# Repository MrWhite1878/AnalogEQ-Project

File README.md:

# AnalogEQ-Project
This repo serves to document relevant information on the design of an analog audio equalizer, whose goal is to serve as a learning tool and correctional component for my desktop speakers.
<!-- Photo -->
> WARNING: This project is a work in progress.
> Nothing is finalized, and this repo mainly serves to document and catalog my journey.

### Target Specifications
*	RCA audio input/output (adapters included)
*	9VAC Wall Wart power input
* ±18VDC rails powering NE5532 and TL072 op amps
* Smooth knobs for all controls
* High input impedance and low output impedance
* Audio bypass switch
* Input and Output Amplification
* 3rd order butterworth BPF for frequencies outside 20Hz-20kHz
* Sharp (Q = 10) -15dB Notch filter with adjustable target frequency (35-85Hz)
* LF and HF shelving with adjustable gain (±16dB) and proportional break/corner frequency
* 2 fully parametric middle controls: ±15dB gain, 70Hz-1.5kHz range 1 and 700-15kHz range 2, 0.5 < Q < 5
* Diagnostic board LEDs and testing pads

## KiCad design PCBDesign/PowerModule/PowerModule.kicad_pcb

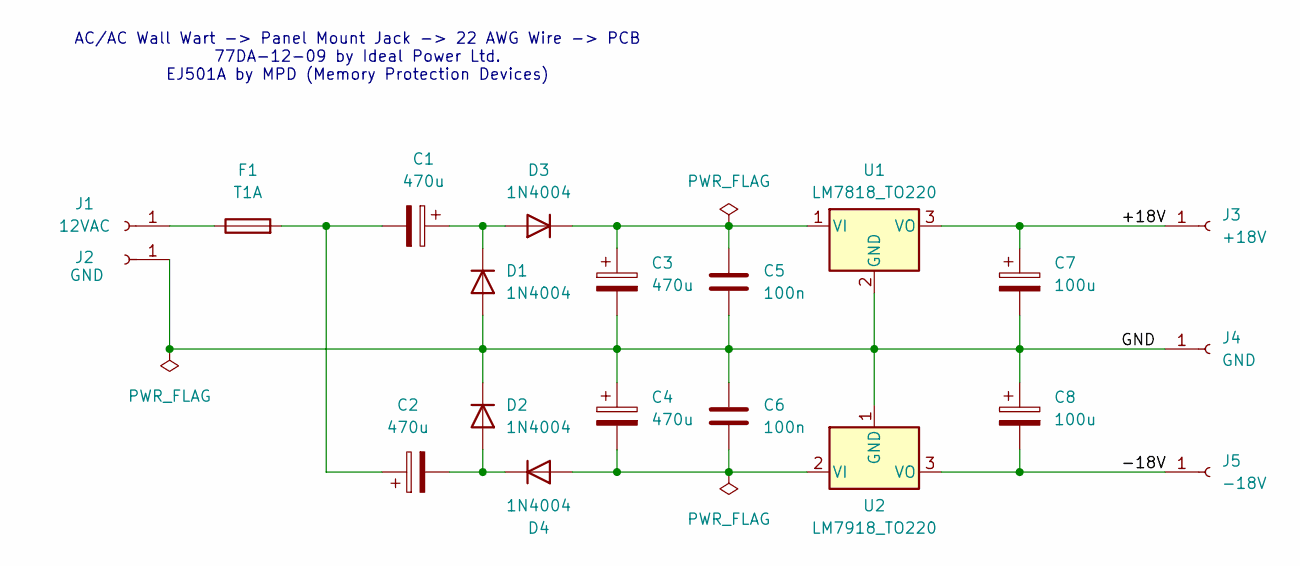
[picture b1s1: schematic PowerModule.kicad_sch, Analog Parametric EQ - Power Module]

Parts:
C1, C2, C3, C4: 470u; CP_Radial_D10.0mm_P5.00mm; MPN 50ZLJ470M10X20
C5, C6: 100n; C_Disc_D3.8mm_W2.6mm_P2.50mm; MPN K104K10X7RF53L2
C7, C8: 100u; CP_Radial_D8.0mm_P3.50mm; MPN 50ZLJ100M8X11.5
D1, D2, D3, D4: 1N4004; D_DO-41_SOD81_P10.16mm_Horizontal; MPN 1N4004G
F1: T1A; Fuse_BelFuse_0697H; MPN 0697H1000-02
J1: 12VAC; SolderWire-0.5sqmm_1x01_D0.9mm_OD2.1mm_Relief
J2, J4: GND; SolderWire-0.5sqmm_1x01_D0.9mm_OD2.1mm_Relief
J3: +18V; SolderWire-0.5sqmm_1x01_D0.9mm_OD2.1mm_Relief
J5: -18V; SolderWire-0.5sqmm_1x01_D0.9mm_OD2.1mm_Relief
U1: LM7818_TO220; TO-220-3_Vertical; MPN MC7818CTG
U2: LM7918_TO220; TO-220-3_Vertical; MPN MC7918CTG

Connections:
/+18V: C7.1, J3.1 (Pin_1_1), U1.3 (VO)
/-18V: C8.2, J5.1 (Pin_1_1), U2.3 (VO)
/GND: C3.2, C4.1, C5.2, C6.1, C7.2, C8.1, D1.2 (A), D2.1 (K), J2.1 (Pin_1_1), J4.1 (Pin_1_1), U1.2 (GND), U2.1 (GND)
unnamed: C1.2, C2.1, F1.2
unnamed: C1.1, D1.1 (K), D3.2 (A)
unnamed: C2.2, D2.2 (A), D4.1 (K)
unnamed: C3.1, C5.1, D3.1 (K), U1.1 (VI)
unnamed: C4.2, C6.2, D4.2 (A), U2.2 (VI)
unnamed: F1.1, J1.1 (Pin_1_1)

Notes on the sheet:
AC/AC Wall Wart -> Panel Mount Jack -> 22 AWG Wire -> PCB 77DA-12-09 by Ideal Power Ltd. EJ501A by MPD (Memory Protection Devices)

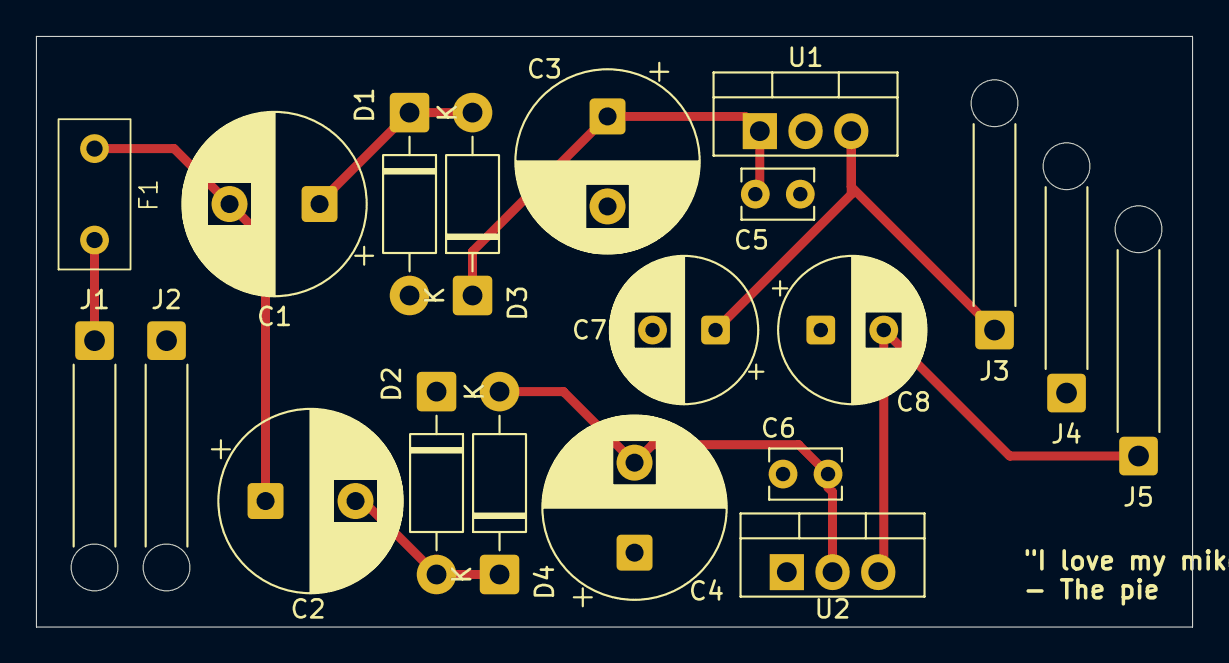
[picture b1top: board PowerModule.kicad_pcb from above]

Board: 2 copper layers, 64.2 x 32.8 mm, 20 parts (0 on the bottom side), 9 nets.

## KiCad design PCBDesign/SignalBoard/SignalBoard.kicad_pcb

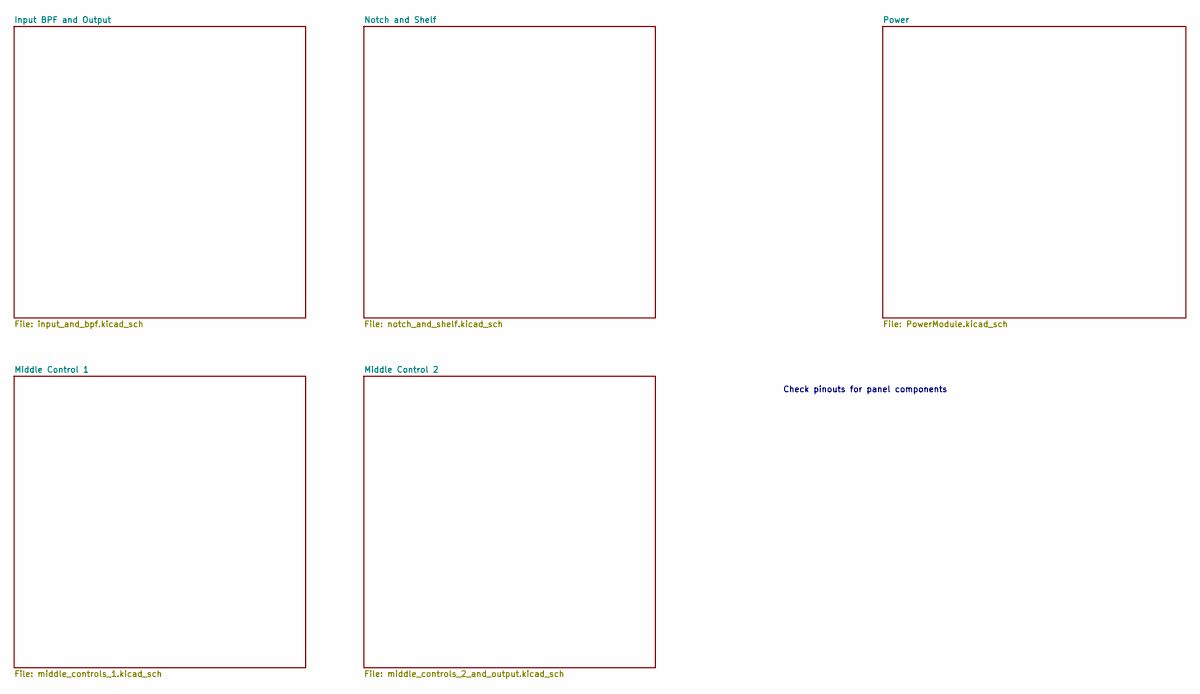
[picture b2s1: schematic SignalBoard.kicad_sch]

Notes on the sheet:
Check pinouts for panel components

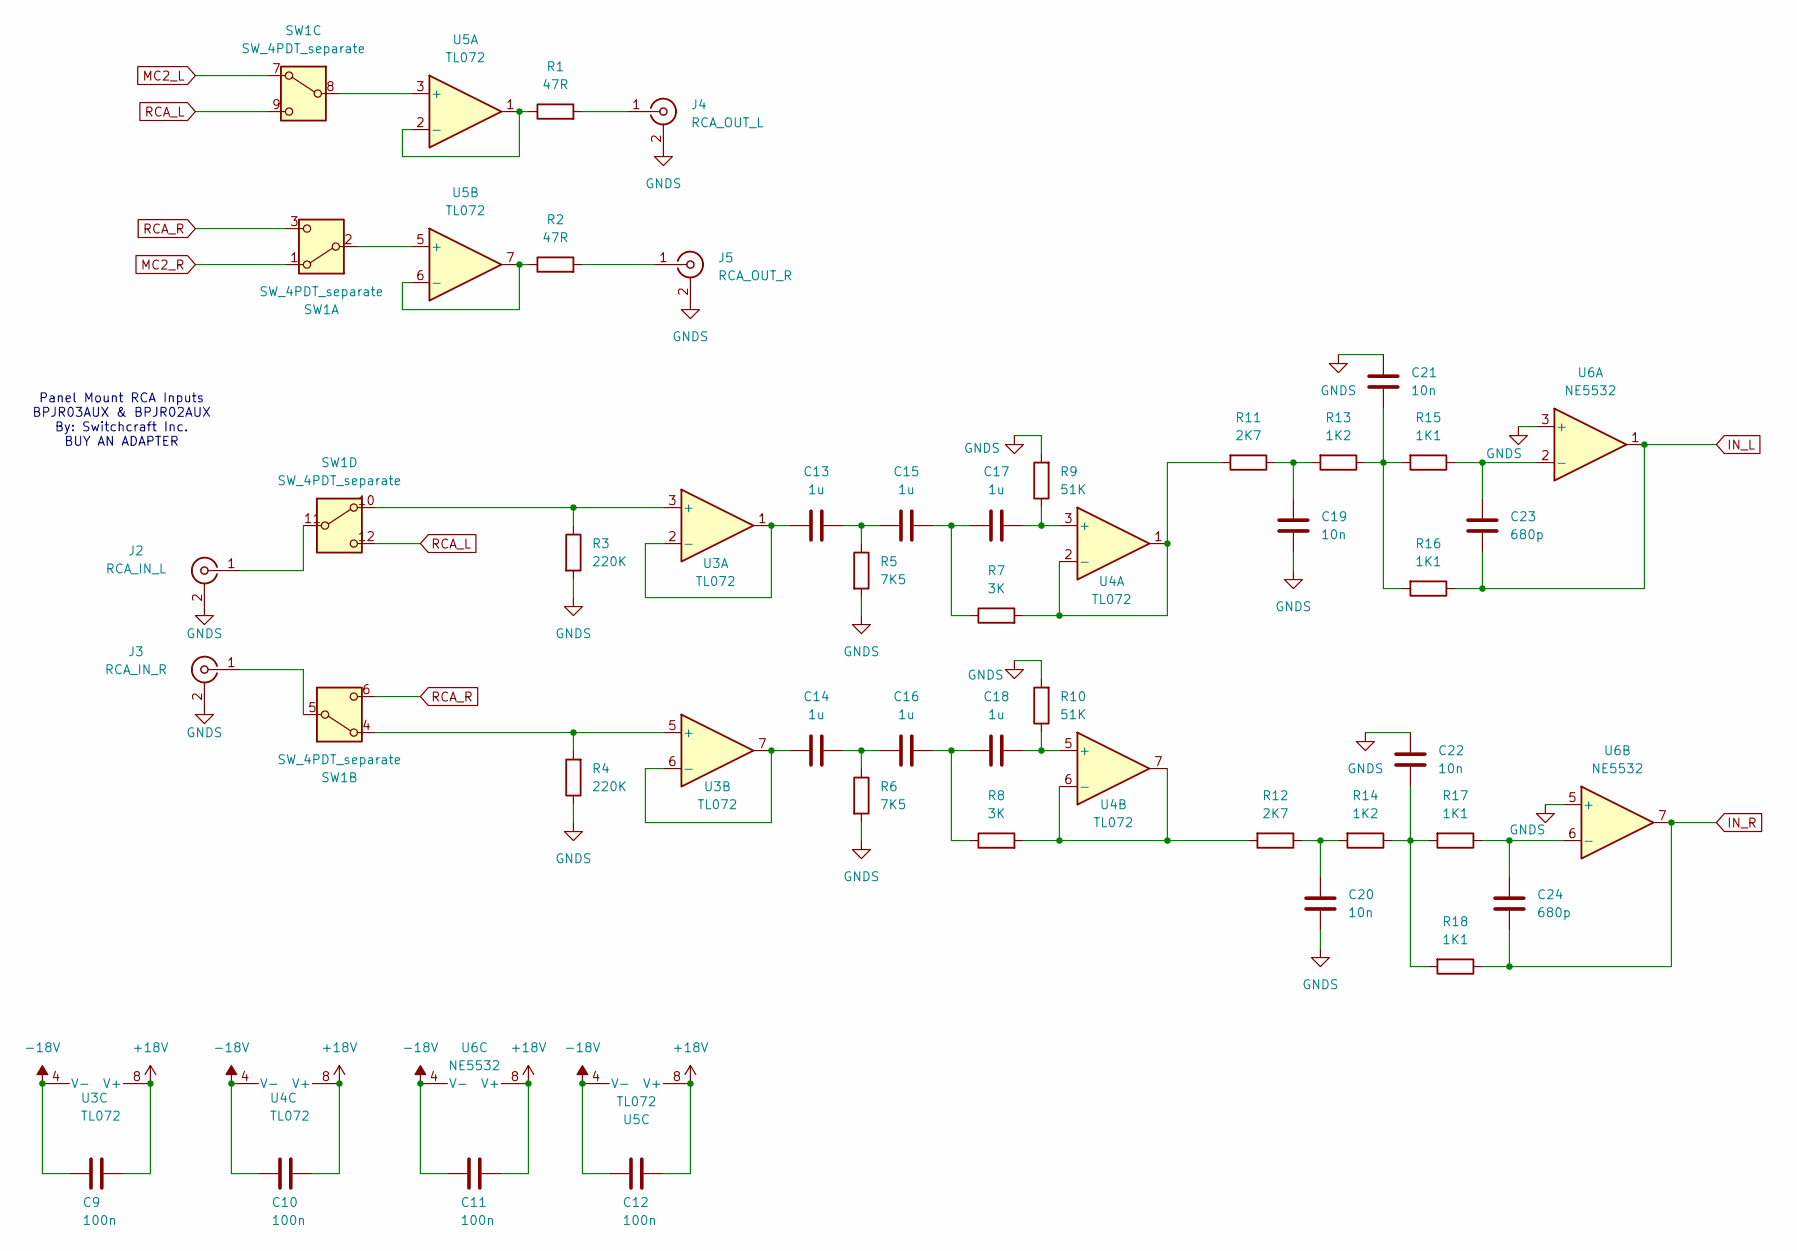
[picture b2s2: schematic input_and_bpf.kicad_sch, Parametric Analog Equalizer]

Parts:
C9, C10, C11, C12: 100n; C_0805_2012Metric_Pad1.18x1.45mm_HandSolder; MPN CL21B104KCFNNNE; Digikey PN 1276-6840-1-ND
C13, C14, C15, C16, C17, C18: 1u; C_Rect_L18.0mm_W7.0mm_P15.00mm_FKS3_FKP3; MPN ECW-FE2W105JA
C19, C20, C21, C22: 10n; C_1206_3216Metric_Pad1.33x1.80mm_HandSolder; MPN CC1206JKNPO0BN103; Digikey PN 311-4374-1-ND
C23, C24: 680p; C_1206_3216Metric_Pad1.33x1.80mm_HandSolder; MPN CC1206JRNPOYBN681; Digikey PN 13-CC1206JRNPOYBN681CT-ND
J2: RCA_IN_L; KLPX-0848A-2-; MPN KLPX-0848A-2-W
J3: RCA_IN_R; KLPX-0848A-2-; MPN KLPX-0848A-2-R
J4: RCA_OUT_L; KLPX-0848A-2-; MPN KLPX-0848A-2-W
J5: RCA_OUT_R; KLPX-0848A-2-; MPN KLPX-0848A-2-R
R1, R2: 47R; R_1206_3216Metric_Pad1.30x1.75mm_HandSolder; MPN RT1206FRE0747RL; Digikey PN 13-RT1206FRE0747RLCT-ND
R3, R4: 220K; R_1206_3216Metric_Pad1.30x1.75mm_HandSolder; MPN RT1206FRE07220KL; Digikey PN 13-RT1206FRE07220KLCT-ND
R5, R6: 7K5; R_1206_3216Metric_Pad1.30x1.75mm_HandSolder; MPN RT1206FRE077K5L; Digikey PN 13-RT1206FRE077K5LCT-ND
R7, R8: 3K; R_1206_3216Metric_Pad1.30x1.75mm_HandSolder; MPN RT1206DRD073KL; Digikey PN 13-RT1206DRD073KLCT-ND
R9, R10: 51K; R_1206_3216Metric_Pad1.30x1.75mm_HandSolder; MPN RT1206DRD0751KL; Digikey PN 13-RT1206DRD0751KLCT-ND
R11, R12: 2K7; R_1206_3216Metric_Pad1.30x1.75mm_HandSolder; MPN RT1206DRE072K7L; Digikey PN 311-2985-1-ND
R13, R14: 1K2; R_1206_3216Metric_Pad1.30x1.75mm_HandSolder; MPN RT1206FRE071K2L; Digikey PN 13-RT1206FRE071K2LCT-ND
R15, R16, R17, R18: 1K1; R_1206_3216Metric_Pad1.30x1.75mm_HandSolder; MPN RT1206FRE071K1L; Digikey PN 13-RT1206FRE071K1LCT-ND
SW1: SW_4PDT_separate; 1004P1T1B9M7QEH; MPN 1004P1T1B9M7QEH
U3, U4, U5: TL072; DIP-8_W7.62mm_LongPads; MPN TL072BCP
U6: NE5532; DIP-8_W7.62mm_LongPads; MPN NE5532P

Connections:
+18V: C9.1, C10.1, C11.1, C12.1, U3.8 (V+), U4.8 (V+), U5.8 (V+), U6.8 (V+); also elsewhere on the board
-18V: C9.2, C10.2, C11.2, C12.2, U3.4 (V-), U4.4 (V-), U5.4 (V-), U6.4 (V-); also elsewhere on the board
GNDS: C19.2, C20.2, C21.1, C22.1, J2.2 (Ext), J3.2 (Ext), J4.2 (Ext), J5.2 (Ext), R3.2, R4.1, R5.2, R6.2, R9.2, R10.2, U6.3 (+), U6.5 (+); also elsewhere on the board
IN_L: C23.2, R16.1, U6.1; also elsewhere on the board
IN_R: C24.2, R18.1, U6.7; also elsewhere on the board
MC2_L: SW1.7 (A); also elsewhere on the board
MC2_R: SW1.1 (A); also elsewhere on the board
unnamed: C13.2, C15.1, R5.1
unnamed: C14.2, C16.1, R6.1
unnamed: C15.2, C17.1, R7.1
unnamed: C16.2, C18.1, R8.1
unnamed: C19.1, R11.1, R13.2
unnamed: C20.1, R12.1, R14.2
unnamed: C21.2, R13.1, R15.2, R16.2
unnamed: C22.2, R14.1, R17.2, R18.2
unnamed: J2.1 (In), SW1.11 (B)
unnamed: J3.1 (In), SW1.5 (B)
unnamed: J4.1 (In), R1.2
unnamed: J5.1 (In), R2.2
unnamed: SW1.2 (B), U5.5 (+)
unnamed: R4.2, SW1.4 (A), U3.5 (+)
unnamed: SW1.8 (B), U5.3 (+)
unnamed: R3.1, SW1.10 (A), U3.3 (+)
unnamed: C13.1, U3.1, U3.2 (-)
unnamed: C14.1, U3.6 (-), U3.7
unnamed: C17.2, R9.1, U4.3 (+)
unnamed: R7.2, R11.2, U4.1, U4.2 (-)
unnamed: C18.2, R10.1, U4.5 (+)
unnamed: R8.2, R12.2, U4.6 (-), U4.7
unnamed: R1.1, U5.1, U5.2 (-)
unnamed: R2.1, U5.6 (-), U5.7
unnamed: C23.1, R15.1, U6.2 (-)
unnamed: C24.1, R17.1, U6.6 (-)
RCA_L: SW1.9 (C), SW1.12 (C)
RCA_R: SW1.3 (C), SW1.6 (C)

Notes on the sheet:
Panel Mount RCA Inputs BPJR03AUX & BPJR02AUX By: Switchcraft Inc. BUY AN ADAPTER

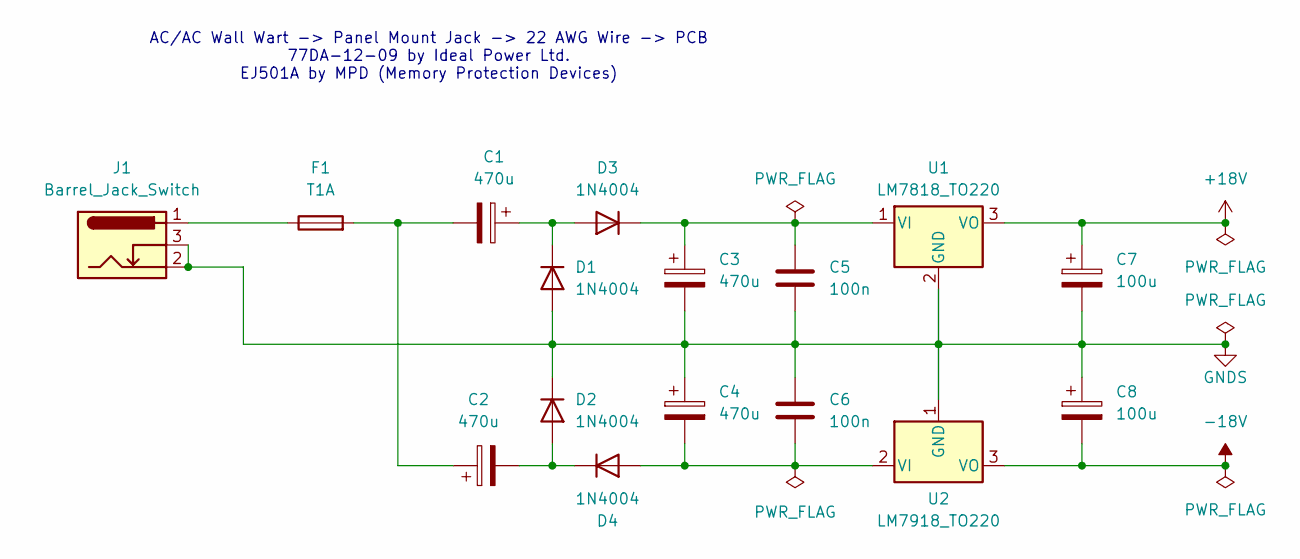
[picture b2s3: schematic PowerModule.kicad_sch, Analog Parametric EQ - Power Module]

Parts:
C1, C2, C3, C4: 470u; CP_Radial_D10.0mm_P5.00mm; MPN 50ZLJ470M10X20
C5, C6: 100n; C_Disc_D3.8mm_W2.6mm_P2.50mm; MPN K104K10X7RF53L2
C7, C8: 100u; CP_Radial_D8.0mm_P3.50mm; MPN 50ZLJ100M8X11.5
D1, D2, D3, D4: 1N4004; D_DO-41_SOD81_P10.16mm_Horizontal; MPN 1N4004G; Digikey PN 1N4004GOS-ND
F1: T1A; Fuse_BelFuse_0697H; MPN 0697H1000-02; Digikey PN 5923-0697H1000-02CT-ND
J1: Barrel_Jack_Switch; 54-00127; MPN 54-00127
U1: LM7818_TO220; TO-220-3_Vertical; MPN MC7818CTG
U2: LM7918_TO220; TO-220-3_Vertical; MPN MC7918CTG

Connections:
+18V: C7.1, U1.3 (VO); also elsewhere on the board
-18V: C8.2, U2.3 (VO); also elsewhere on the board
GNDS: C3.2, C4.1, C5.2, C6.1, C7.2, C8.1, D1.2 (A), D2.1 (K), J1.2, J1.3, U1.2 (GND), U2.1 (GND); also elsewhere on the board
unnamed: C1.2, C2.1, F1.2
unnamed: C1.1, D1.1 (K), D3.2 (A)
unnamed: C2.2, D2.2 (A), D4.1 (K)
unnamed: C3.1, C5.1, D3.1 (K), U1.1 (VI)
unnamed: C4.2, C6.2, D4.2 (A), U2.2 (VI)
unnamed: F1.1, J1.1

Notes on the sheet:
AC/AC Wall Wart -> Panel Mount Jack -> 22 AWG Wire -> PCB 77DA-12-09 by Ideal Power Ltd. EJ501A by MPD (Memory Protection Devices)

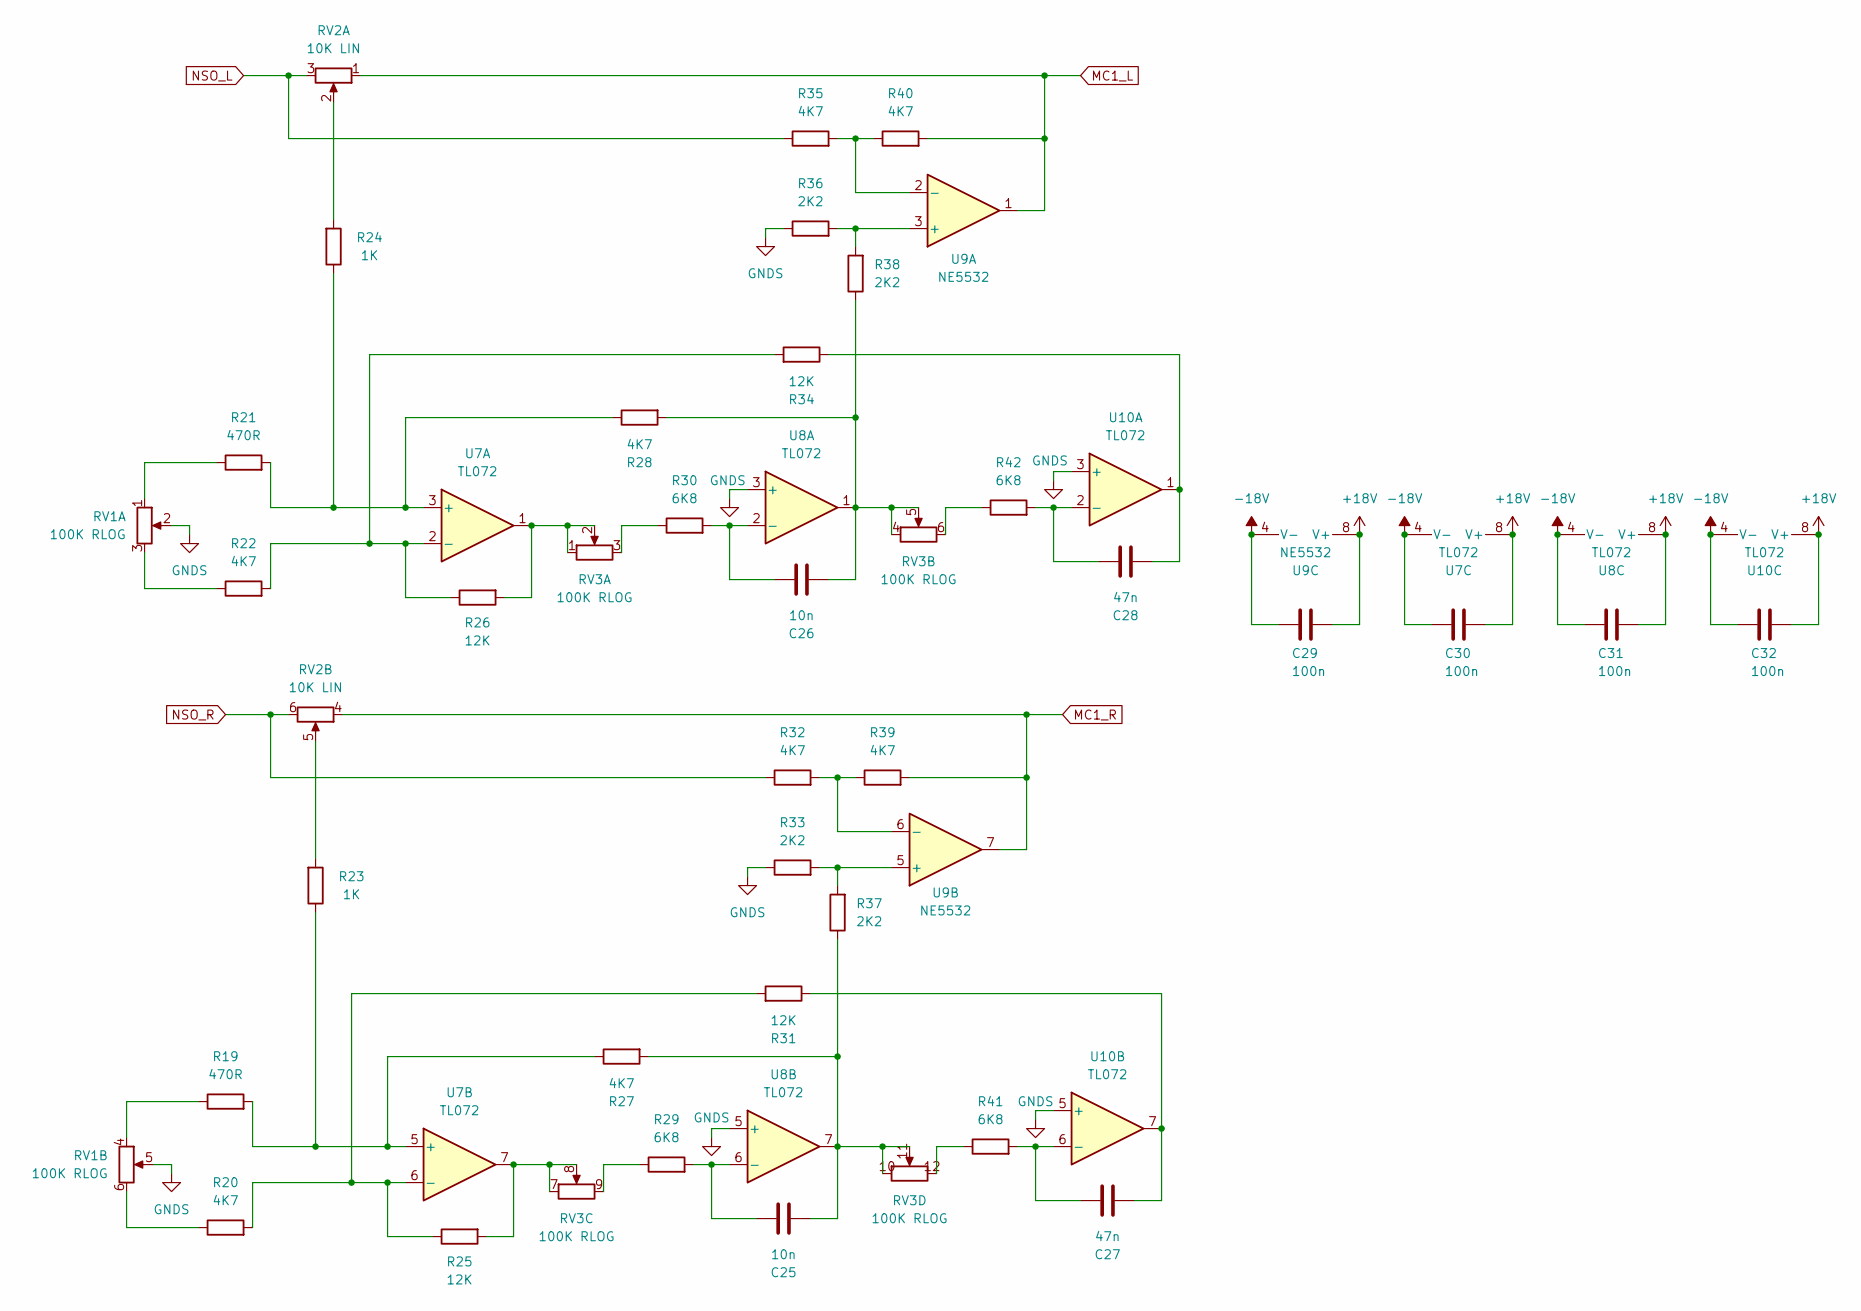
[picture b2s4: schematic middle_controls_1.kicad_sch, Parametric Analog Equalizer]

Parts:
C25, C26: 10n; C_1206_3216Metric_Pad1.33x1.80mm_HandSolder; MPN CC1206JKNPO0BN103; Digikey PN 311-4374-1-ND
C27, C28: 47n; C_Rect_L7.2mm_W3.5mm_P5.00mm_FKS2_FKP2_MKS2_MKP2; MPN PHE426DJ5470JR05
C29, C30, C31, C32: 100n; C_0805_2012Metric_Pad1.18x1.45mm_HandSolder; MPN CL21B104KCFNNNE; Digikey PN 1276-6840-1-ND
R19, R21: 470R; R_1206_3216Metric_Pad1.30x1.75mm_HandSolder; MPN RT1206DRE07470RL; Digikey PN 311-2995-1-ND
R20, R22, R27, R28, R32, R35, R39, R40: 4K7; R_1206_3216Metric_Pad1.30x1.75mm_HandSolder; MPN RT1206DRD074K7L; Digikey PN 13-RT1206DRD074K7LCT-ND
R23, R24: 1K; R_1206_3216Metric_Pad1.30x1.75mm_HandSolder; MPN RT1206DRD071KL; Digikey PN 311-2925-1-ND
R25, R26, R31, R34: 12K; R_1206_3216Metric_Pad1.30x1.75mm_HandSolder; MPN RT1206DRE0712KL; Digikey PN 311-2960-1-ND
R29, R30, R41, R42: 6K8; R_1206_3216Metric_Pad1.30x1.75mm_HandSolder; MPN RT1206DRD076K8L; Digikey PN 13-RT1206DRD076K8LCT-ND
R33, R36, R37, R38: 2K2; R_1206_3216Metric_Pad1.30x1.75mm_HandSolder; MPN RT1206DRE072K2L; Digikey PN 311-2984-1-ND
RV1: 100K RLOG; PTD902-2215K-B103; MPN PTD902-2015K-C104
RV2: 10K LIN; PTD902-2215K-B103; MPN PTD902-2215K-B103
RV3: 100K RLOG; PTD904-2015K-C104; MPN PTD904-2015K-C104
U7, U8, U10: TL072; DIP-8_W7.62mm_LongPads; MPN TL072BCP
U9: NE5532; DIP-8_W7.62mm_LongPads; MPN NE5532P

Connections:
+18V: C29.1, C30.1, C31.1, C32.1, U7.8 (V+), U8.8 (V+), U9.8 (V+), U10.8 (V+); also elsewhere on the board
-18V: C29.2, C30.2, C31.2, C32.2, U7.4 (V-), U8.4 (V-), U9.4 (V-), U10.4 (V-); also elsewhere on the board
GNDS: R33.1, R36.1, RV1.2, RV1.5, U8.3 (+), U8.5 (+), U10.3 (+), U10.5 (+); also elsewhere on the board
MC1_L: R40.2, RV2.1, U9.1; also elsewhere on the board
MC1_R: R39.2, RV2.4, U9.7; also elsewhere on the board
NSO_L: R35.1, RV2.3; also elsewhere on the board
NSO_R: R32.1, RV2.6; also elsewhere on the board
unnamed: C25.2, R27.2, R37.1, RV3.10, RV3.11, U8.7
unnamed: C26.2, R28.2, R38.1, RV3.4, RV3.5, U8.1
unnamed: C27.2, R31.1, U10.7
unnamed: C28.2, R34.1, U10.1
unnamed: R19.1, RV1.4
unnamed: R20.1, RV1.6
unnamed: R21.1, RV1.1
unnamed: R22.1, RV1.3
unnamed: R23.2, RV2.5
unnamed: R24.2, RV2.2
unnamed: R25.2, RV3.7, RV3.8, U7.7
unnamed: R26.2, RV3.1, RV3.2, U7.1
unnamed: R29.1, RV3.9
unnamed: R30.1, RV3.3
unnamed: R41.1, RV3.12
unnamed: R42.1, RV3.6
unnamed: R21.2, R24.1, R28.1, U7.3 (+)
unnamed: R22.2, R26.1, R34.2, U7.2 (-)
unnamed: R19.2, R23.1, R27.1, U7.5 (+)
unnamed: R20.2, R25.1, R31.2, U7.6 (-)
unnamed: C26.1, R30.2, U8.2 (-)
unnamed: C25.1, R29.2, U8.6 (-)
unnamed: R36.2, R38.2, U9.3 (+)
unnamed: R35.2, R40.1, U9.2 (-)
unnamed: R33.2, R37.2, U9.5 (+)
unnamed: R32.2, R39.1, U9.6 (-)
unnamed: C28.1, R42.2, U10.2 (-)
unnamed: C27.1, R41.2, U10.6 (-)

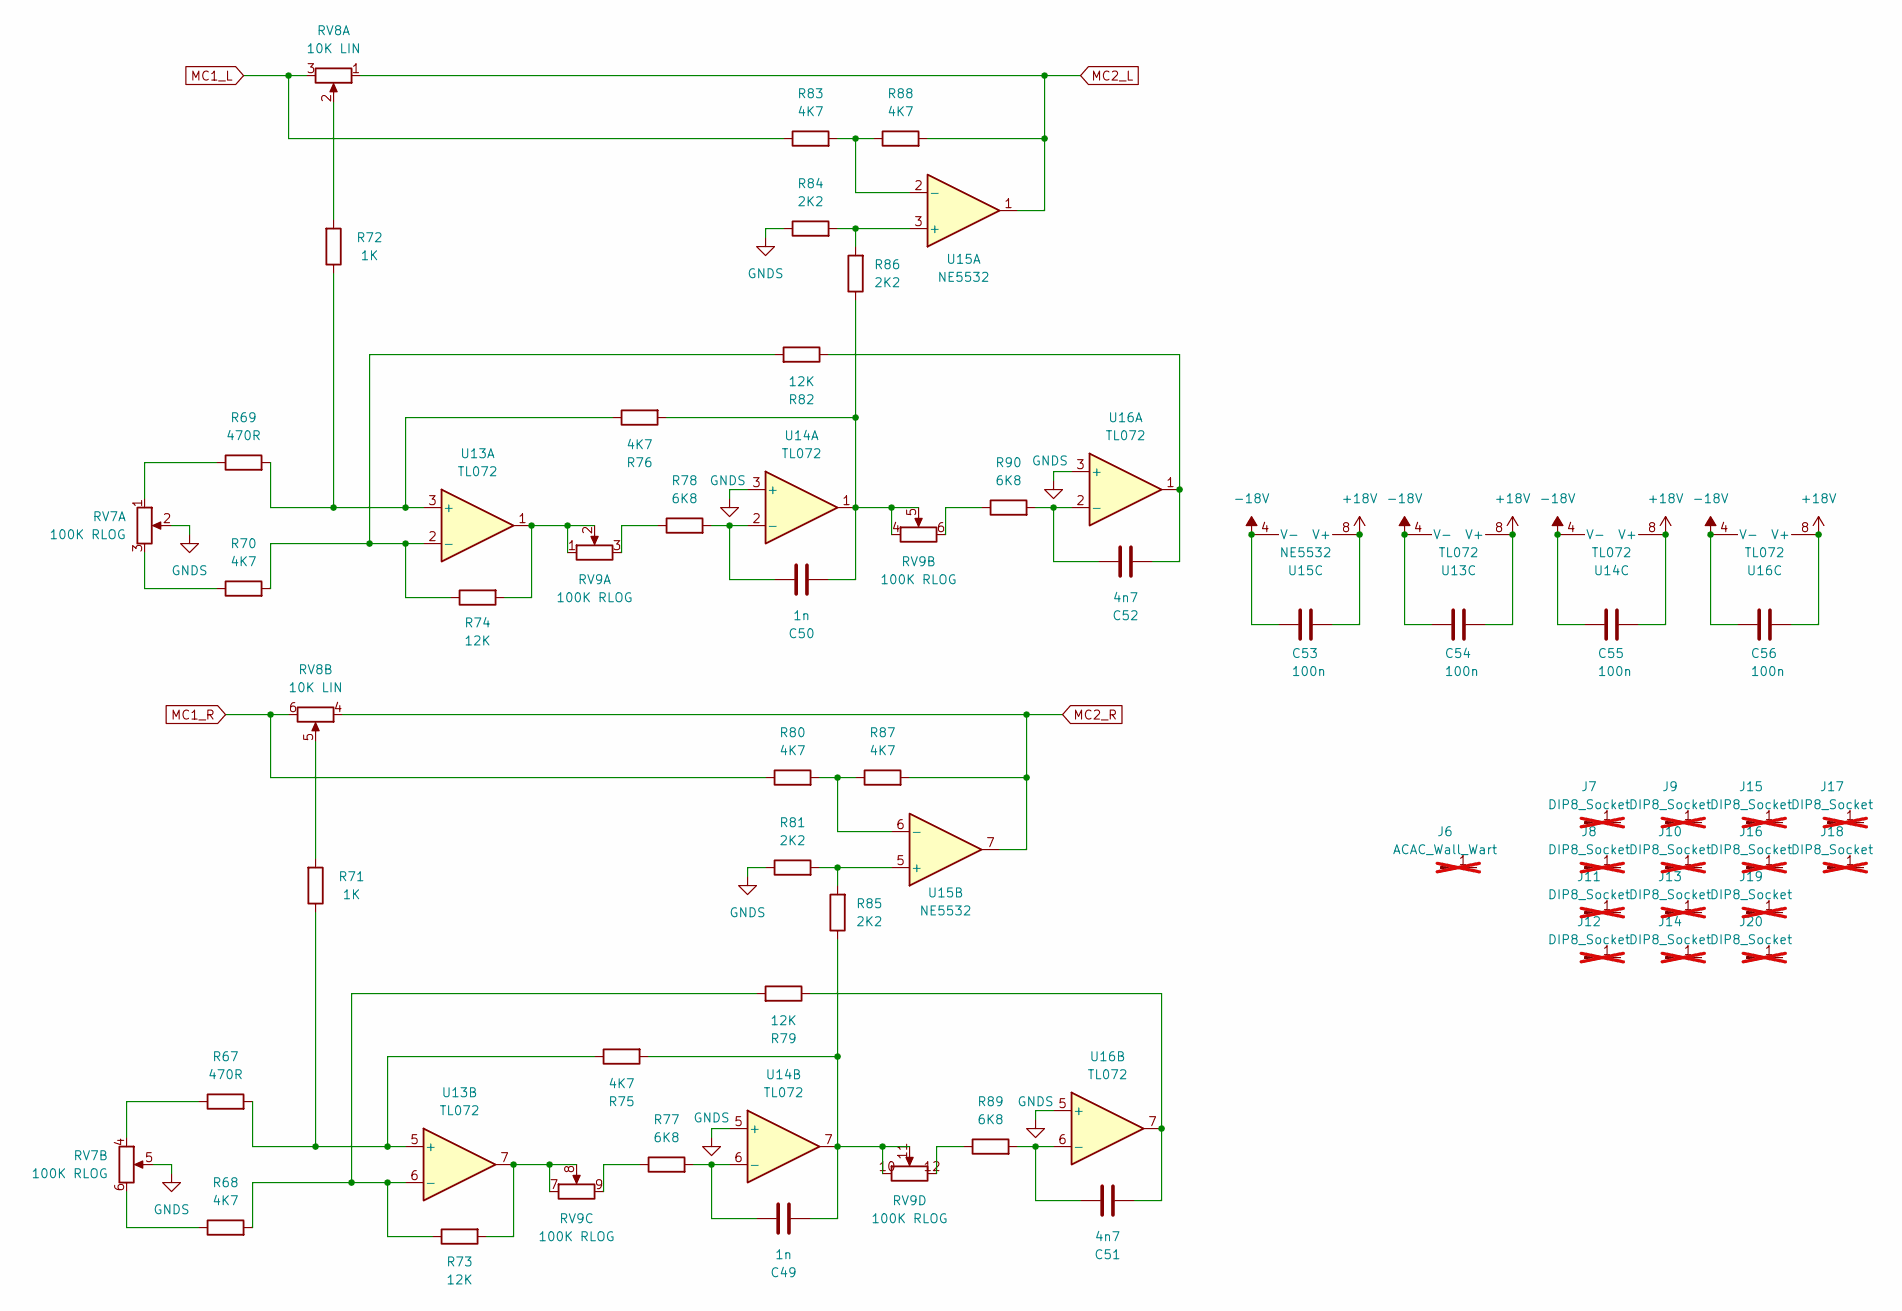
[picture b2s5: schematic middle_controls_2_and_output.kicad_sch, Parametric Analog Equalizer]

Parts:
C49, C50: 1n; C_1206_3216Metric_Pad1.33x1.80mm_HandSolder; MPN CC1206JRNPOBBN102; Digikey PN 13-CC1206JRNPOBBN102CT-ND
C51, C52: 4n7; C_1206_3216Metric_Pad1.33x1.80mm_HandSolder; MPN CC1206JRNPO0BN472; Digikey PN 311-4403-1-ND
C53, C54, C55, C56: 100n; C_0805_2012Metric_Pad1.18x1.45mm_HandSolder; MPN CL21B104KCFNNNE; Digikey PN 1276-6840-1-ND
J6: ACAC_Wall_Wart; MPN 77DA-12-09; not fitted
J7, J8, J9, J10, J11, J12, J13, J14, J15, J16, J17, J18, J19, J20: DIP8_Socket; MPN ICS-308-T; Digikey PN 2057-ICS-308-T-ND; not fitted
R67, R69: 470R; R_1206_3216Metric_Pad1.30x1.75mm_HandSolder; MPN RT1206DRE07470RL; Digikey PN 311-2995-1-ND
R68, R70, R75, R76, R80, R83, R87, R88: 4K7; R_1206_3216Metric_Pad1.30x1.75mm_HandSolder; MPN RT1206DRD074K7L; Digikey PN 13-RT1206DRD074K7LCT-ND
R71, R72: 1K; R_1206_3216Metric_Pad1.30x1.75mm_HandSolder; MPN RT1206DRD071KL; Digikey PN 311-2925-1-ND
R73, R74, R79, R82: 12K; R_1206_3216Metric_Pad1.30x1.75mm_HandSolder; MPN RT1206DRE0712KL; Digikey PN 311-2960-1-ND
R77, R78, R89, R90: 6K8; R_1206_3216Metric_Pad1.30x1.75mm_HandSolder; MPN RT1206DRD076K8L; Digikey PN 13-RT1206DRD076K8LCT-ND
R81, R84, R85, R86: 2K2; R_1206_3216Metric_Pad1.30x1.75mm_HandSolder; MPN RT1206DRE072K2L; Digikey PN 311-2984-1-ND
RV7: 100K RLOG; PTD902-2215K-B103; MPN PTD902-2015K-C104
RV8: 10K LIN; PTD902-2215K-B103; MPN PTD902-2215K-B103
RV9: 100K RLOG; PTD904-2015K-C104; MPN PTD904-2015K-C104
U13, U14, U16: TL072; DIP-8_W7.62mm_LongPads; MPN TL072BCP
U15: NE5532; DIP-8_W7.62mm_LongPads; MPN NE5532P

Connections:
+18V: C53.1, C54.1, C55.1, C56.1, U13.8 (V+), U14.8 (V+), U15.8 (V+), U16.8 (V+); also elsewhere on the board
-18V: C53.2, C54.2, C55.2, C56.2, U13.4 (V-), U14.4 (V-), U15.4 (V-), U16.4 (V-); also elsewhere on the board
GNDS: R81.1, R84.1, RV7.2, RV7.5, U14.3 (+), U14.5 (+), U16.3 (+), U16.5 (+); also elsewhere on the board
MC1_L: R83.1, RV8.3; also elsewhere on the board
MC1_R: R80.1, RV8.6; also elsewhere on the board
MC2_L: R88.2, RV8.1, U15.1; also elsewhere on the board
MC2_R: R87.2, RV8.4, U15.7; also elsewhere on the board
unnamed: C49.2, R75.2, R85.1, RV9.10, RV9.11, U14.7
unnamed: C50.2, R76.2, R86.1, RV9.4, RV9.5, U14.1
unnamed: C51.2, R79.1, U16.7
unnamed: C52.2, R82.1, U16.1
unnamed: R67.1, RV7.4
unnamed: R68.1, RV7.6
unnamed: R69.1, RV7.1
unnamed: R70.1, RV7.3
unnamed: R71.2, RV8.5
unnamed: R72.2, RV8.2
unnamed: R73.2, RV9.7, RV9.8, U13.7
unnamed: R74.2, RV9.1, RV9.2, U13.1
unnamed: R77.1, RV9.9
unnamed: R78.1, RV9.3
unnamed: R89.1, RV9.12
unnamed: R90.1, RV9.6
unnamed: R69.2, R72.1, R76.1, U13.3 (+)
unnamed: R70.2, R74.1, R82.2, U13.2 (-)
unnamed: R67.2, R71.1, R75.1, U13.5 (+)
unnamed: R68.2, R73.1, R79.2, U13.6 (-)
unnamed: C50.1, R78.2, U14.2 (-)
unnamed: C49.1, R77.2, U14.6 (-)
unnamed: R84.2, R86.2, U15.3 (+)
unnamed: R83.2, R88.1, U15.2 (-)
unnamed: R81.2, R85.2, U15.5 (+)
unnamed: R80.2, R87.1, U15.6 (-)
unnamed: C52.1, R90.2, U16.2 (-)
unnamed: C51.1, R89.2, U16.6 (-)

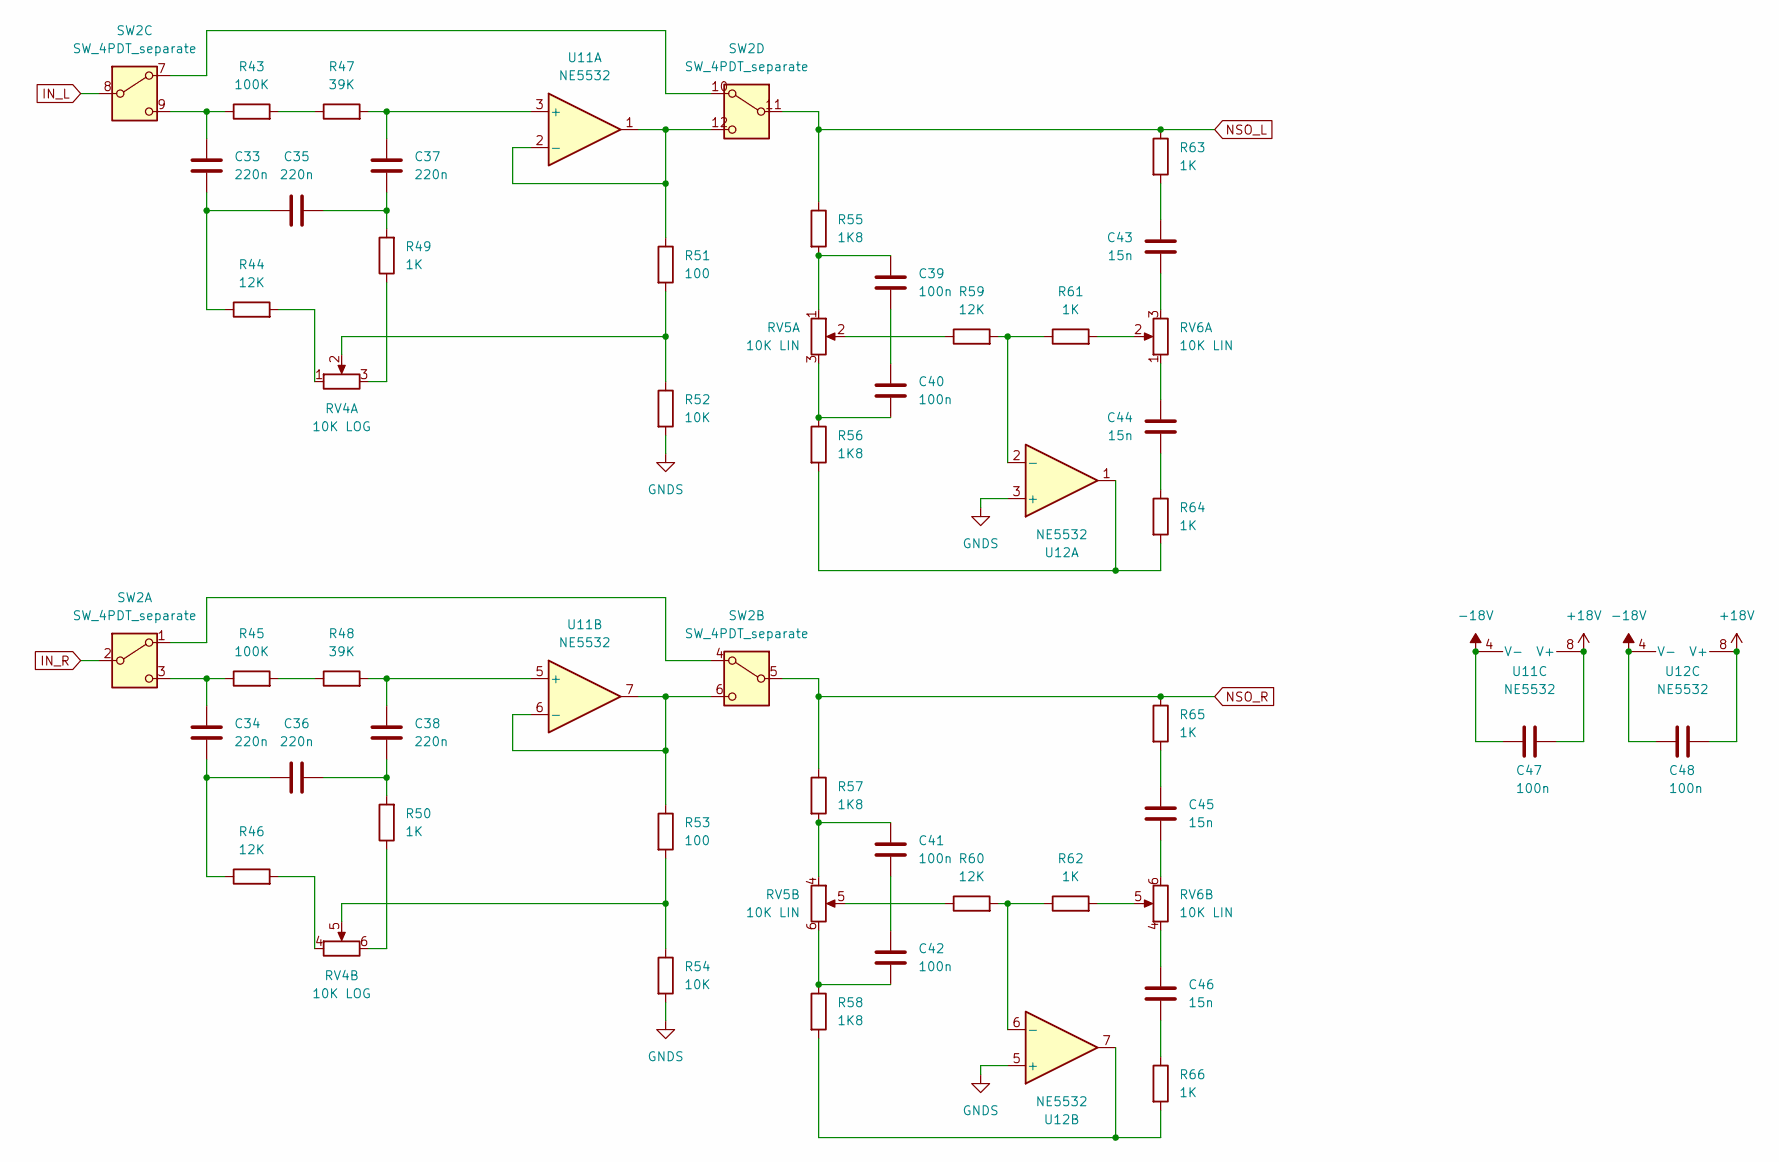
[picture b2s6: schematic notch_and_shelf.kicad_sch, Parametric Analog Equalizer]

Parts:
C33, C34, C35, C36, C37, C38: 220n; C_Rect_L13.0mm_W6.0mm_P10.00mm_FKS3_FKP3_MKS4; MPN PHE426HA6220JR05
C39, C40, C41, C42: 100n; C_Rect_L7.2mm_W6.0mm_P5.00mm; MPN PHE426HJ6100JR05
C43, C44, C45, C46: 15n; C_Rect_L7.2mm_W2.5mm_P5.00mm_FKS2_FKP2_MKS2_MKP2; MPN PHE426DJ5150JR05
C47, C48: 100n; C_0805_2012Metric_Pad1.18x1.45mm_HandSolder; MPN CL21B104KCFNNNE; Digikey PN 1276-6840-1-ND
R43, R45: 100K; R_1206_3216Metric_Pad1.30x1.75mm_HandSolder; MPN RT1206DRD07100KL; Digikey PN 311-2914-1-ND
R44, R46, R59, R60: 12K; R_1206_3216Metric_Pad1.30x1.75mm_HandSolder; MPN RT1206DRE0712KL; Digikey PN 311-2960-1-ND
R47, R48: 39K; R_1206_3216Metric_Pad1.30x1.75mm_HandSolder; MPN RT1206DRE0739KL; Digikey PN 311-2991-1-ND
R49, R50, R61, R62, R63, R64, R65, R66: 1K; R_1206_3216Metric_Pad1.30x1.75mm_HandSolder; MPN RT1206DRD071KL; Digikey PN 311-2925-1-ND
R51, R53: 100; R_1206_3216Metric_Pad1.30x1.75mm_HandSolder; MPN RT1206DRD07100RL; Digikey PN 311-2915-1-ND
R52, R54: 10K; R_1206_3216Metric_Pad1.30x1.75mm_HandSolder; MPN RT1206DRD0710KL; Digikey PN 311-2916-1-ND
R55, R56, R57, R58: 1K8; R_1206_3216Metric_Pad1.30x1.75mm_HandSolder; MPN RT1206FRE071K8L; Digikey PN 13-RT1206FRE071K8LCT-ND
RV4: 10K LOG; PDB182-K415K-103A1; MPN PDB182-K415K-103A1
RV5, RV6: 10K LIN; PTD902-2215K-B103; MPN PTD902-2215K-B103
SW2: SW_4PDT_separate; 1004P1T1B9M7QEH; MPN 1004P1T1B9M7QEH
U11, U12: NE5532; DIP-8_W7.62mm_LongPads; MPN NE5532P

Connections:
+18V: C47.1, C48.1, U11.8 (V+), U12.8 (V+); also elsewhere on the board
-18V: C47.2, C48.2, U11.4 (V-), U12.4 (V-); also elsewhere on the board
GNDS: R52.2, R54.2, U12.3 (+), U12.5 (+); also elsewhere on the board
IN_L: SW2.8 (B); also elsewhere on the board
IN_R: SW2.2 (B); also elsewhere on the board
NSO_L: R55.1, R63.1, SW2.11 (B); also elsewhere on the board
NSO_R: R57.1, R65.1, SW2.5 (B); also elsewhere on the board
unnamed: C33.2, C35.1, R44.1
unnamed: C34.2, C36.1, R46.1
unnamed: C35.2, C37.2, R49.2
unnamed: C36.2, C38.2, R50.2
unnamed: C39.1, R55.2, RV5.1
unnamed: C39.2, C40.1
unnamed: C40.2, R56.1, RV5.3
unnamed: C41.1, R57.2, RV5.4
unnamed: C41.2, C42.1
unnamed: C42.2, R58.1, RV5.6
unnamed: C43.1, R63.2
unnamed: C43.2, RV6.3
unnamed: C44.1, RV6.1
unnamed: C44.2, R64.1
unnamed: C45.1, R65.2
unnamed: C45.2, RV6.6
unnamed: C46.1, RV6.4
unnamed: C46.2, R66.1
unnamed: R43.2, R47.1
unnamed: R44.2, RV4.1
unnamed: R45.2, R48.1
unnamed: R46.2, RV4.4
unnamed: R49.1, RV4.3
unnamed: R50.1, RV4.6
unnamed: R51.2, R52.1, RV4.2
unnamed: R53.2, R54.1, RV4.5
unnamed: R56.2, R64.2, U12.1
unnamed: R58.2, R66.2, U12.7
unnamed: R59.1, RV5.2
unnamed: R60.1, RV5.5
unnamed: R61.2, RV6.2
unnamed: R62.2, RV6.5
unnamed: SW2.1 (A), SW2.4 (A)
unnamed: C34.1, R45.1, SW2.3 (C)
unnamed: R53.1, SW2.6 (C), U11.6 (-), U11.7
unnamed: SW2.7 (A), SW2.10 (A)
unnamed: C33.1, R43.1, SW2.9 (C)
unnamed: R51.1, SW2.12 (C), U11.1, U11.2 (-)
unnamed: C37.1, R47.2, U11.3 (+)
unnamed: C38.1, R48.2, U11.5 (+)
unnamed: R59.2, R61.1, U12.2 (-)
unnamed: R60.2, R62.1, U12.6 (-)

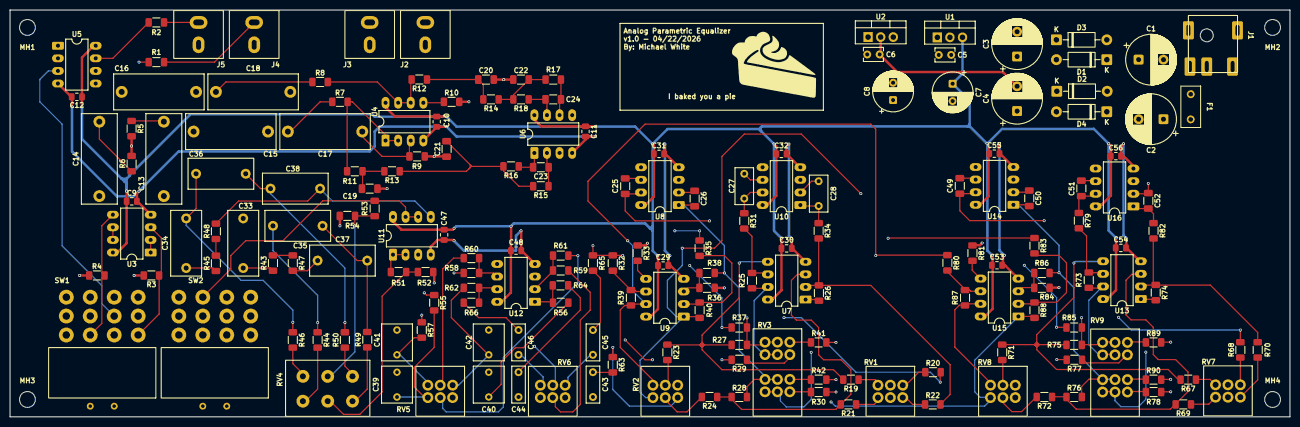
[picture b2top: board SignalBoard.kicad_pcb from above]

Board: 4 copper layers, 258.0 x 82.0 mm, 187 parts (0 on the bottom side), 143 nets.

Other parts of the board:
MH1, MH2, MH3, MH4: MountingHole_3.2mm_M3_ISO7380

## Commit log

2026-03-06 Expand README with project details and timeline
    Added detailed project specifications, file table of contents, and project timeline.
2026-03-06 Created folder structure using placeholder files
2026-03-06 Update file table of contents in README.md with links to folders
2026-03-06 Update README with new section titles and formatting
2026-03-06 Updated README specs and created specs&motives in design doc
2026-03-06 Add rule to ignore temporary files
2026-03-13 LTspice schematics for LPF, HPF, bell, and shelving filters
2026-03-27 Add rule to ignore raw files in .gitignore
2026-03-27 Improved filters and added notes
2026-04-17 Updated file structure, readme, add KiCad schematics with real components and notes
